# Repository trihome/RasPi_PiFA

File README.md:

# PiFA HAT

This board will make it possible to connect equipment used at the factory  (ex: switches, sensors, relays, at all...) to your Raspberry Pi.
It can isolate connected equipments from Raspberry Pi.

**Note**

Please import this library before using this repository.
https://github.com/trihome/KiCad_MyLibrary

**How to make**

[Manual (Japanese only)](./doc/README_pcb.jp.md)

## [PiFA 8xy](./PiFA_8xy/)

A prototyping board "HAT".
GPIO pins can be freely selected.

- 4 isolated inputs and 4 isolated outputs.
- Selectable Sink(NPN) / Source(PNP)
- I2C-bus voltage-level translator (3.3 to 5 V)
- RTC

## License

This is under [CC-BY-SA](https://creativecommons.org/licenses/by-sa/4.0/).

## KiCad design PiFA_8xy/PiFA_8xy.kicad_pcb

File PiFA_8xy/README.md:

# PiFA 8xy

A prototyping board "HAT".

GPIO pins can be freely selected.

[Schematic](./img/PiFA_8xy.pdf)

**Note**

Please import this library before using this repository.
https://github.com/trihome/KiCad_MyLibrary

## Spec

- 4 isolated inputs and 4 isolated outputs.
  - J3(Y) is Output, and J5(X) is Input.
  - Connect these connectors to the Raspberry Pi Pins.
  - [J3 and J5: B4B-XH-A(LF)(SN)](http://akizukidenshi.com/catalog/g/gC-12249/)
  - [Raspberry Pi Pins: QI(2550)connectors](http://akizukidenshi.com/catalog/g/gC-12150/)
- Supply 24V power to J7.
  - J2 is Input / Output for FA(24V)
  - Recommended [Terminal block](https://www.togi.co.jp/product/interface/1072/) and [Cables](https://www.togi.co.jp/product/harness-cable/2661/) or QI(2550)connectors.
- Selectable Sink(NPN) / Source(PNP) : J1(Input), J4(Output)
  - U6: Transistor array, you have to choose.
    - J4 = [Sink(NPN)](http://akizukidenshi.com/catalog/g/gI-10669/)
    - J4 = [Source(PNP)](http://akizukidenshi.com/catalog/g/gI-10957/)
- I2C-bus voltage-level translator (3.3 to 5 V)
  - [U1: AE-PCA9306](http://akizukidenshi.com/catalog/g/gM-05452/)
  - I2C Output connector
    - J6: Pin Header (5V)
    - J8: GROVE (5V)
- RTC
  - [U4 : DS1307+](http://akizukidenshi.com/catalog/g/gI-06949/)
  - [BT1: CH243-2032LF](http://akizukidenshi.com/catalog/g/gP-02019/) and CR2032

## Example of use

### Terminal block

- [Terminal block](https://www.togi.co.jp/product/interface/1072/)
- [Cables](https://www.togi.co.jp/product/harness-cable/2661/)

### Stack
If you need more I/O ports, you can increase them by stacking boards.

- The board sandwiched in the middle is [Grove Base Hat for Raspberry Pi](http://wiki.seeedstudio.com/Grove_Base_Hat_for_Raspberry_Pi/)
- DIN rail bracket: [example](https://www.takachi-el.co.jp/products/DRA)

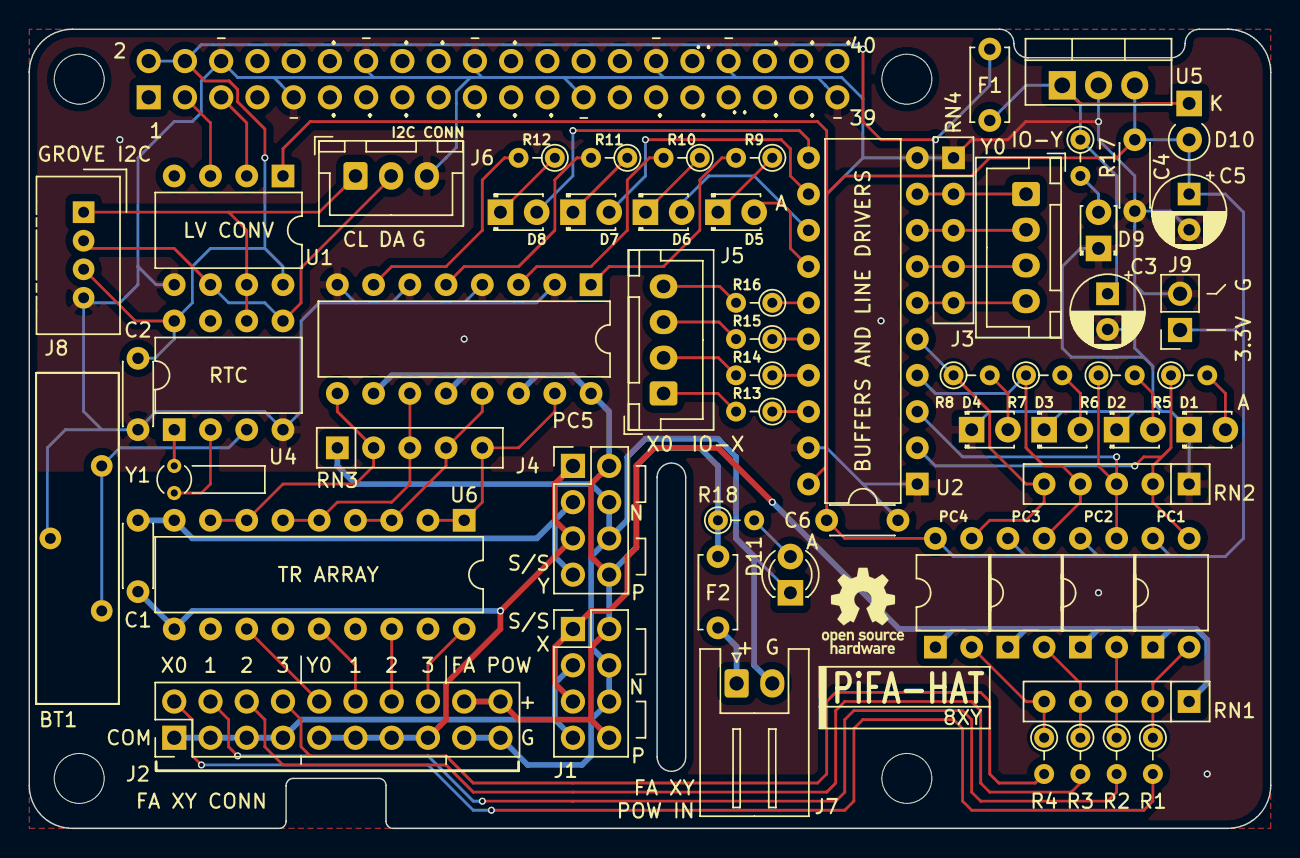
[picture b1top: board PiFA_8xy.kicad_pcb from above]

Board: 2 copper layers, 87.0 x 56.0 mm, 69 parts (1 on the bottom side), 68 nets.

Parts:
BT1: CH74-2032LF; BatteryHolder_Keystone_CH74-2032LF
C1, C2, C4: 0.1uF; C_Disc_D4.3mm_W1.9mm_P5.00mm
C3: 100uF; CP_Radial_D5.0mm_P2.50mm
C5: 470uF; CP_Radial_D5.0mm_P2.50mm
C6: 0.1u; C_Disc_D4.3mm_W1.9mm_P5.00mm
D1, D2, D3, D4: LED-G; LED_D1.8mm_W3.3mm_H2.4mm
D5, D6, D7, D8: LED-Y; LED_D1.8mm_W3.3mm_H2.4mm
D9: LED-R; LED_D1.8mm_W3.3mm_H2.4mm
D10: D; D_A-405_P2.54mm_Vertical_KathodeUp
D11: LED-R; LED_D3.0mm
F1: 0.17A(MAX0.34); C_Disc_D5.0mm_W2.5mm_P5.00mm
F2: 0.25A(MAX0.5); C_Disc_D5.0mm_W2.5mm_P5.00mm
H1: MountingHole; OSHW-Logo_5.7x6mm_SilkScreen
H2: MountingHole; CC-BY-SA
J1: S/S SelX; PinHeader_2x04_P2.54mm_Vertical
J2: IO CONN; PinHeader_2x10_P2.54mm_Vertical
J3: Y CONN; JST_XH_B4B-XH-A_1x04_P2.50mm_Vertical
J4: S/S SelY; PinHeader_2x04_P2.54mm_Vertical
J5: X CONN; JST_XH_B4B-XH-A_1x04_P2.50mm_Vertical
J6: I2C 5V; JST_XH_B3B-XH-A_1x03_P2.50mm_Vertical
J7: Pow24V; JST_XH_S2B-XH-A_1x02_P2.50mm_Horizontal
J8: GROVE I2C; NS-Tech_Grove_1x04_P2mm_Vertical
J9: Out3.3V; PinSocket_1x02_P2.54mm_Vertical
MH1, MH2, MH3, MH4: MountingHole; MountingHole_3mm
P1: RasPi CONN; PinSocket_2x20_P2.54mm_Vertical
PC1, PC2, PC3, PC4: FOD814A300W; DIP-4_W7.62mm
PC5: TLP627-4; DIP-16_W7.62mm
R1, R2, R3, R4, R18: 4.7k; R_Axial_DIN0204_L3.6mm_D1.6mm_P2.54mm_Vertical
R5, R6, R7, R8, R13, R14, R15, R16, R17: 1k; R_Axial_DIN0204_L3.6mm_D1.6mm_P2.54mm_Vertical
R9, R10, R11, R12: 100; R_Axial_DIN0204_L3.6mm_D1.6mm_P2.54mm_Vertical
RN1, RN2: 4.7k; R_Array_SIP5
RN3: 10k; R_Array_SIP5
RN4: 1k; R_Array_SIP5
U1: AE-PCA9306; DIP-8_W7.62mm
U2: 74HCT541; DIP-20_W7.62mm
U4: DS1307+; DIP-8_W7.62mm
U5: 78033_TO220; TO-220-3_Vertical
U6: TBD62083APG; DIP-18_W7.62mm
Y1: 32.767kHz; Crystal_Round_D2.0mm_Vertical

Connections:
+3V3: C4.1, C5.1, C6.1, D10.2, J9.1, PC1.4, PC2.4, PC3.4, PC4.4, U1.1, U2.20, U5.3
+5V: C2.1, F1.2, J8.3, P1.2, P1.4, U1.8, U4.8
+24V: F2.1, J1.2, J1.8, J2.18, J2.20, J4.2, J4.8, PC5.10, PC5.12, PC5.14, PC5.16, R18.1
/+24V_X: J1.1, J1.5, PC1.1, PC2.1, PC3.1, PC4.1, RN1.1
/+24V_Y: C1.2, J2.9, J2.11, J2.13, J2.15, J4.1, J4.5, U6.10
/GNDD_X: J1.3, J1.7, J2.1, J2.3, J2.5, J2.7
/GNDD_Y: C1.1, J4.3, J4.7, U6.9
/GPIO2(SDA1): P1.3, U1.3
/GPIO3(SCL1): P1.5, U1.2
/SCL: J6.1, J8.1, U1.7, U4.6
/SDA: J6.2, J8.2, U1.6, U4.5
/Xo00: J2.2, R1.2
/Xo01: J2.4, R2.2
/Xo02: J2.6, R3.2
/Xo03: J2.8, R4.2
/Y00: D8.2, U2.11
/Y01: D7.2, U2.12
/Y02: D6.2, U2.13
/Y03: D5.2, U2.14
/Yo00: J2.10, U6.12
/Yo01: J2.12, U6.14
/Yo02: J2.14, U6.16
/Yo03: J2.16, U6.18
GND: BT1.2, C2.2, C3.2, C4.2, C5.2, C6.2, D1.1, D2.1, D3.1, D4.1, D9.1, J6.3, J8.4, J9.2, P1.6, P1.9, P1.14, P1.20, P1.25, P1.30, P1.34, P1.39, PC5.2, PC5.4, PC5.6, PC5.8, RN2.1, RN4.1, U1.5, U2.1, U2.10, U2.19, U4.4, U5.2
GNDD: D11.1, J1.4, J1.6, J2.17, J2.19, J4.4, J4.6, J7.2, RN3.1
unnamed: BT1.1, U4.3
unnamed: C3.1, D10.1, F1.1, R17.1, U5.1
unnamed: D1.2, R5.2
unnamed: D2.2, R6.2
unnamed: D3.2, R7.2
unnamed: D4.2, R8.2
unnamed: D5.1, R9.1
unnamed: D6.1, R10.1
unnamed: D7.1, R11.1
unnamed: D8.1, R12.1
unnamed: D9.2, R17.2
unnamed: D11.2, R18.2
unnamed: F2.2, J7.1
unnamed: J3.1, RN4.2, U2.9
unnamed: J3.2, RN4.3, U2.8
unnamed: J3.3, RN4.4, U2.7
unnamed: J3.4, RN4.5, U2.6
unnamed: J5.1, R13.2
unnamed: J5.2, R14.2
unnamed: J5.3, R15.2
unnamed: J5.4, R16.2
unnamed: PC1.2, R1.1, RN1.2
unnamed: PC1.3, R5.1, RN2.2, U2.2
unnamed: PC2.2, R2.1, RN1.3
unnamed: PC2.3, R6.1, RN2.3, U2.3
unnamed: PC3.2, R3.1, RN1.4
unnamed: PC3.3, R7.1, RN2.4, U2.4
unnamed: PC4.2, R4.1, RN1.5
unnamed: PC4.3, R8.1, RN2.5, U2.5
unnamed: PC5.1, R9.2
unnamed: PC5.3, R10.2
unnamed: PC5.5, R11.2
unnamed: PC5.7, R12.2
unnamed: PC5.9, RN3.2, U6.7, U6.8
unnamed: PC5.11, RN3.3, U6.5, U6.6
unnamed: PC5.13, RN3.4, U6.3, U6.4
unnamed: PC5.15, RN3.5, U6.1, U6.2
unnamed: R13.1, U2.18
unnamed: R14.1, U2.17
unnamed: R15.1, U2.16
unnamed: R16.1, U2.15
unnamed: U4.1, Y1.1
unnamed: U4.2, Y1.2

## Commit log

2020-03-29 Add files
2020-03-29 Add documentation for U6
2020-03-30 Add and fix documentation
2020-03-30 Add comments
2020-03-30 Fix typos
2020-07-10 Update README.md
    Fix typo in docs.
2020-07-11 License changed.

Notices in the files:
parts and their libraries:
Creative Commons Licence
